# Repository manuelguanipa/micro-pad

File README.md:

# Customizable micro pad

  PCB for a customizable micro pad.
=======

PCB for a customizable micro pad.

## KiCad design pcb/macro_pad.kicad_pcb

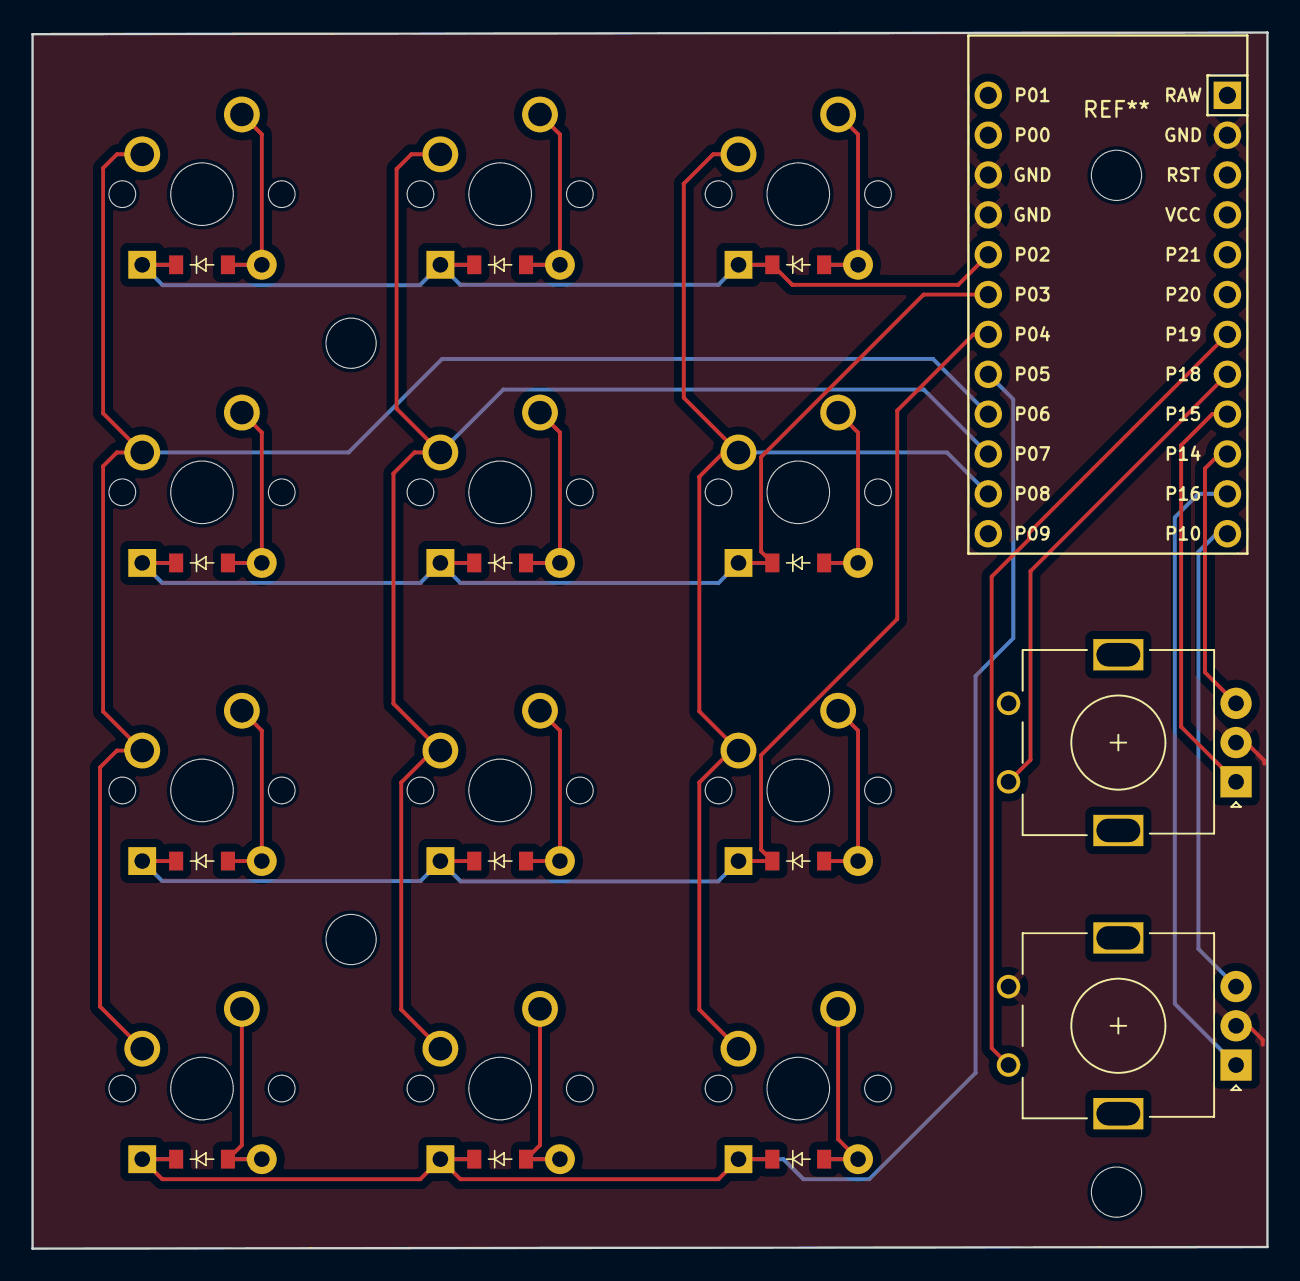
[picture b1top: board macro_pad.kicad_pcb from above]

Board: 2 copper layers, 78.7 x 77.5 mm, 31 parts (1 on the bottom side), 26 nets.

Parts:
 : MountingHole_3.2mm_M3
 #2,  #3: MountingHole_3.2mm_M3
 #4: LOGO
D1, D2, D3, D4, D5, D6, D7, D8, D9, D10, D11, D12: ComboDiode
MCU1: ProMicro
ROT1, ROT2: rotary_encoder
S1, S2, S3, S4, S5, S6, S7, S8, S9, S10, S11, S12: MX

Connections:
GND: MCU1.2, MCU1.15, MCU1.16, ROT1.2, ROT1.C, ROT2.2, ROT2.C
P2: D4.1, D8.1, D12.1, MCU1.17
P3: D3.1, D7.1, D11.1, MCU1.18
P4: D2.1, D6.1, D10.1, MCU1.19
P5: D1.1, D5.1, D9.1, MCU1.20
P6: MCU1.21, S1.2, S2.2, S3.2, S4.2
P7: MCU1.22, S5.2, S6.2, S7.2, S8.2
P8: MCU1.23, S9.2, S10.2, S11.2, S12.2
P10: MCU1.12, ROT1.B
P14: MCU1.10, ROT2.B
P15: MCU1.9, ROT2.A
P16: MCU1.11, ROT1.A
P18: MCU1.8, ROT2.1
P19: MCU1.7, ROT1.1
left_bottom: D1.2, S1.1
left_lower-mid: D2.2, S2.1
left_top: D4.2, S4.1
left_upper-mid: D3.2, S3.1
middle_bottom: D5.2, S5.1
middle_lower-mid: D6.2, S6.1
middle_top: D8.2, S8.1
middle_upper-mid: D7.2, S7.1
right_bottom: D9.2, S9.1
right_lower-mid: D10.2, S10.1
right_top: D12.2, S12.1
right_upper-mid: D11.2, S11.1

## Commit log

2024-02-19 Inital commit
2024-02-19 Fix readme file
2024-02-19 Fix readme name
